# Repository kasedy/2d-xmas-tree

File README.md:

# 2d-xmas-Tree-art
A DIY flat christmas decoration with a ATtiny25, 20 led´s and a coin cell battery 

## New Features
- Converted to [PlatformIo](https://platformio.org/) project
- Uploading firmware and setting fuses get easier
- Added animation compressing script
- Significantly reduced memory footprint
- More default animations
- Reduced power consumption

## Overview

This is the only 2-dimensional pcb with all the components embedded into the 1,6mm thick pcb itself.
The components are placed with the help of castellation into the pcb. 

## PCB

The PCB design is made with KiCad 5.0.1

The PCB should be 1,6mm thick to hide the components inside. Last time I ordered them from [DirtyPCbs](https://dirtypcbs.com/) as suggesed by [@designer2k2](https://github.com/designer2k2). They handle castellation, but you still need to clean metal contacts from bended metalization debris. Next time I'm going to order with [JLCPCB](https://jlcpcb.com/) as I like their bright solder mask color more. To order PCB, use prepared gerber archive [2D_xmas_tree01_gerber_complete.zip](https://raw.githubusercontent.com/kasedy/2d-xmas-tree-art/master/pcb-kicad/gerb/2D_xmas_tree01_gerber_complete.zip)

Most of the PCB is to give it the look of a tree or house, it uses the different color achievable by blending the different layers. Here is a good article on possible colors: https://hackaday.com/2018/06/11/ask-hackaday-what-color-are-your-pcbs/

## Partlist

|ID|#|Ref|Value|Footprint|RS|Digikey|Aliexpress|Img|
| --- | --- | --- | --- | --- | --- | --- | --- | --- |
|BT|2|BT1-BT2|Battery Cell|CR2016|-|-|[CR2016](https://www.aliexpress.com/item/32865072812.html)||
|C|1|C1|22µF|0805|790-0682|1276-6786-1-ND|[0805 22uF capacitor](https://www.aliexpress.com/item/32374775517.html)||
|D|20|D1-D20|LED|0805|176-6117|516-1431-1-ND|[0805 LED](https://www.aliexpress.com/item/1206476683.html)||
|R|5|R1-R5|see table below|0805|-|RR12Q75DCT-ND|[0805 Resistor](https://www.aliexpress.com/item/32865947306.html)||
|R|1|R6|10k|0805|125-1189|RR12P10.0KDCT-ND|[0805 Resistor](https://www.aliexpress.com/item/32865947306.html)||
|SW|1|SW1|SW_SPDT|PCM12SMTR|793-1721|401-2016-1-ND|[MSK-12C02](https://www.aliexpress.com/item/32863424888.html)||
|U|1|U1|ATTINY25-20SU|SOIC8|133-1611|ATTINY25-20SU-ND|-||

ATiny-45 and ATiny-85 will work as well as ATtiny-25 but ATtiny-25 is cheaper and has enough memory to fit the sketch.

## LED

You are free to use any other LED apart proposed above. Please select R1-R5 resistors value according to the table. The lower resistor value the brighter will be LEDs but battery life also will get shorter.

| Nice <br> look | Color | V<sub>min</sub> | V<sub>max</sub> | Non-compensated mode (Ohm) <br> Min - Recomended - Max | Compensated mode (Ohm) <br> Min - Max |
| :---: | :---: | :---: | :---: | :---: | :---: |
| :x: | Red | 1.70 | 2.00 | 150 - 330 - 680 | 30 - 50 |
| :heavy_check_mark: | Yellow | 1.80 | 2.05 | 125 - 180 - 250 | 30 - 50 |
| :heavy_check_mark: | Orange | 1.80 | 2.05 | 125 - 180 - 250 | 30 - 50 |
| :x: | Green | 2.10 | 3.30 | 330 - 680 - 1800 | 30 - 75 |
| :heavy_check_mark: | White | 2.40 | 3.10 | 100 - 470 - 680 | 15 - 60 |
| :heavy_check_mark: | Blue | 2.40 | 3.25 | 100 - 330 - 1000 | 8 - 100 |

In a compensated mode LEDs will have the same brightness regardless how many LEDs are shining. Every enabled LED will shine no more than 1/20 of animation frame time. Resistors should give up to 10-15 mA through a single LED. In non-compensated mode the animation frame with a single LED on will look brighter than an animation with multiple LEDs on. Resistors should give up to 2-4 mA current through a single LED. Non-compensated brightness mode is a default as it gives almost the same brightness for animation frames with high number LEDs enabled, but frames with low number active LEDs look much brighter for the same current consumption from a battery. To change the mode update value of COMPENSATED_BRIGHTNESS flag.

## Assembly

Assembly might be a little challenging. The full process can be seen in this [youtube video](https://www.youtube.com/watch?v=K6z7--RqQHQ). I'll mention here only the tricky parts.

Solder the LED oriented with the cathode to the line, like it's shown on the picture. If you by some reason soldered LEDs upside down and animation looks weird, set REVERSED_LEDS flag to "true" when compile the firmware.

The ATtiny feet needs to be trimmed very closely to the body to fit it inside the cutout.

Use very thin wire to create a kind of spider web for the battery, but don't shortcut it!

Then use some tape to secure it in place.

## Upload Firmware

- Install [PlatformIo](https://platformio.org/)
- Download and open the project at "firmware" directory
- Connect ISP programmer head
- Run "Set Fuses" and "Upload" under "attiny25_1MHz" build rule

To program ATtiny microcontroller ISP programmer is needed. For example an open-source [USB ASP](https://www.fischl.de/usbasp/). As an alternative some Arduinos can be converted to a ISP programmer with ArduinoISP https://www.arduino.cc/en/Tutorial/ArduinoISP.

ISP Pinout:

## Create your own animation!

Use [graphical interface](https://kasedy.github.io/2d-xmas-tree-art/) to create unique animation. Copy every frame value into [animation.txt](firmware/src/animation.txt). After animation is ready compile and upload the firmware.

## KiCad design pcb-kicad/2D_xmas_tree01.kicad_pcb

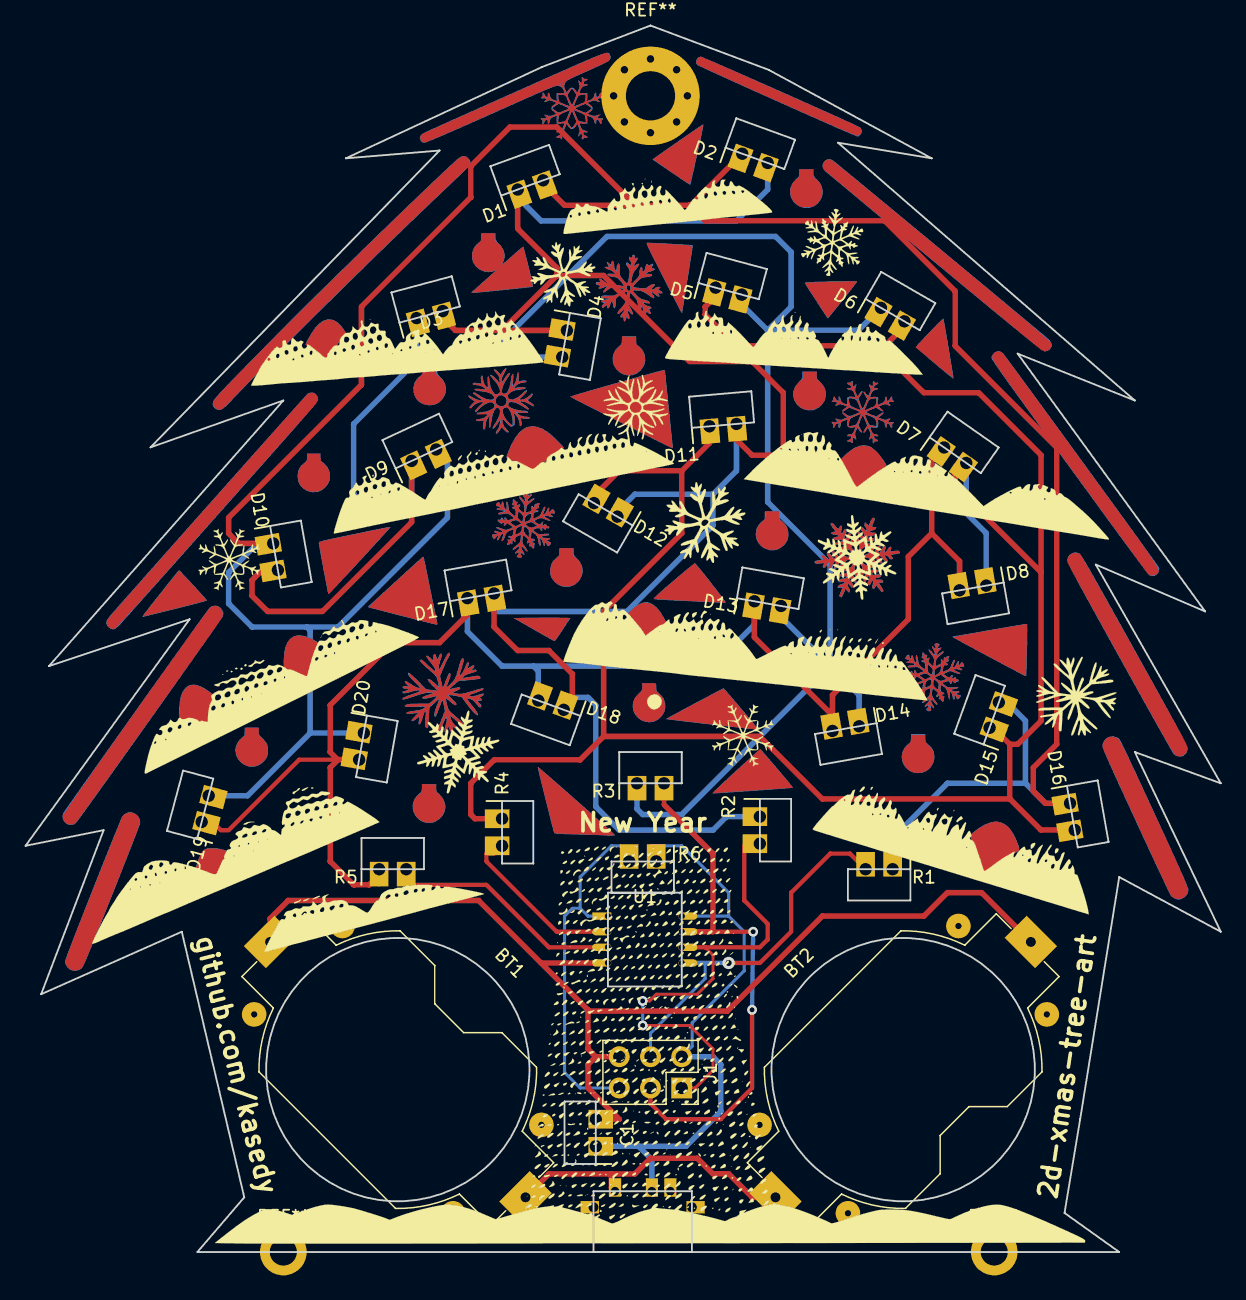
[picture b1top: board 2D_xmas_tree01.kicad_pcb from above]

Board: 2 copper layers, 97.2 x 99.7 mm, 32 parts (0 on the bottom side), 14 nets.

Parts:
BT1, BT2: Battery_Cell; Keystone_1058_1x2032-CoinCell_Inside
C1: C; 0805_Internal_Castellation
D1, D2, D3, D4, D5, D6, D7, D8, D9, D10, D11, D12, D13, D14, D15, D16, D17, D18, D19, D20: LED; 0805_Internal_Castellation
J1: ISP; Socket_Strip_Straight_2x03_Pitch2.54mm
R1, R2, R3, R4, R5: R; 0805_Internal_Castellation
R6: 10k; 0805_Internal_Castellation
SW1: SW_SPDT; PCM12SMTR_inside
U1: ATTINY25-20SU; SOIC-8_Inside

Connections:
/MISO: J1.1, R2.2, U1.6
/MOSI: J1.4, R1.2, U1.5
/RESET: J1.5, R6.2, U1.1
/SCK: J1.3, R3.2, U1.7
/VCC: C1.1, J1.2, R6.1, SW1.2, U1.8
GND: BT1.2, BT2.2, C1.2, J1.6, U1.4
unnamed: BT1.1, BT2.1, SW1.1
unnamed: D1.1, D2.2, D3.2, D4.1, D11.2, D12.1, D17.2, D18.1, R2.1
unnamed: D1.2, D2.1, D9.2, D10.1, D15.2, D16.1, D19.2, D20.1, R1.1
unnamed: D3.1, D4.2, D5.2, D6.1, D9.1, D10.2, D13.2, D14.1, R3.1
unnamed: D5.1, D6.2, D7.2, D8.1, D11.1, D12.2, D15.1, D16.2, R4.1
unnamed: D7.1, D8.2, D13.1, D14.2, D17.1, D18.2, D19.1, D20.2, R5.1
unnamed: R4.2, U1.2
unnamed: R5.2, U1.3

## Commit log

2019-10-26 Replaced 2018 year on a silk with "Merry Xmas"
2019-11-16 Reduced memory footprint to: 1624 bytes / 53 byts
2019-11-16 * Reduced memory footprint to: 1582 bytes / 53 byts
2019-11-16 Reduced memory footprint to: 1558 bytes / 53 byts
2019-11-16 Reduced memory footprint to: 1343 bytes / 53 byts
2019-11-16 Improved readability
2019-11-16 Improved power saving
2019-11-16 updated animation
2019-11-16 Reduced memory footprint to: 1334 bytes / 53 byts
2019-11-16 Converted to platformio project
2019-11-16 Reduced blinking. It is especially noticeable for CPU less than 1MHz
2019-11-16 Added code comments
2019-11-16 added comments
2019-11-16 Measured power consumption. Update the documents.
2019-11-16 fixed warning
2019-11-16 Added compiler script for animation
2019-11-16 Changing blink params
2019-11-17 Added snow effect some speed optimizations
2019-11-17 1. added fastRandom to reduce flickering and memory footprint 2. added 2 new animation 3. More comments
2019-11-17 Some renaming
2019-11-17 updated comments
2019-11-17 Changed silk layer to include name of the project that anyone who get the pcb know where to find firmware update
2019-11-17 Display "From Alex & Valery" of the silk layer of the PCB
2019-11-29 Added test animation on the startup. Added flag in REVERSED_LEDS to set true in case if you soldered LED upside down.
2019-12-01 added COMPENSATED BRIGHTNESS LED mode
2019-12-01 comments
2019-12-02 added Resistor value table
2019-12-22 Added CR2160 part list image
2019-12-22 Added part list image for 0805 capacitor
2019-12-22 updated part list images
2019-12-22 updated list part images
2019-12-22 Updated docs
2019-12-22 update img
2020-01-05 Allow to disable test animation
2020-01-05 fixed constants
2020-02-03 added ArduinoISP to configuration
